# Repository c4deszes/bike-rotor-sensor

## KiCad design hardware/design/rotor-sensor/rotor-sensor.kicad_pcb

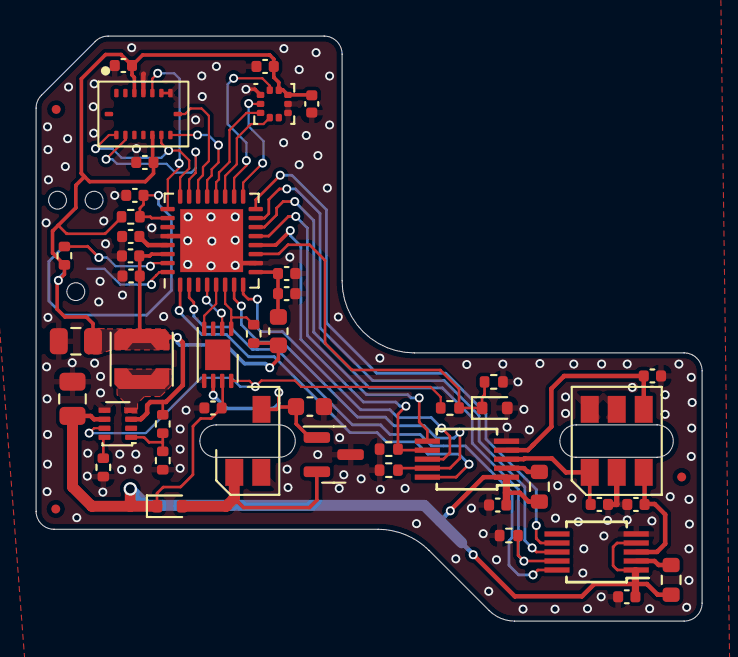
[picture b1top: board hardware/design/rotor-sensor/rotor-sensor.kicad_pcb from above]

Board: 2 copper layers, 37.0 x 32.5 mm, 50 parts (1 on the bottom side), 41 nets.

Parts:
C1, C2, C3, C6, C8, C9, C12, C15, C20, C23, C27, C600, C601: 100n; C_0402_1005Metric
C4, C5: 10u; C_0402_1005Metric
C7: 2.2u; C_0402_1005Metric
C10: 220p; C_0603_1608Metric
C11: 22u; C_0805_2012Metric
C16: 10u; C_0805_2012Metric
D1: BAS3005B02; D_SOD-523
D2: MM5Z3V6T1G; D_SOD-523
D4: SDT23C15L02; SOT-23
FID1, FID3, FID4: Fiducial; Fiducial_0.5mm_Mask1mm
J1: Conn_ARM_SWD_TagConnect_TC2030-NL; Tag-Connect_TC2030-IDC-NL_2x03_P1.27mm_Vertical
J2: Conn_01x06; SOIC-6
L1: 10uH; L_0603_1608Metric
L3: 2.2u; L_Coilcraft_LPS3010
R1, R3, R4, R6, R15, R17: 4.7k; R_0402_1005Metric
R2: 47k; R_0402_1005Metric
R5: 20k; R_0402_1005Metric
R7: 0; R_0402_1005Metric
R9, R18: 63.4k; R_0603_1608Metric
R12: 1k; R_0402_1005Metric
R13: 10k; R_0402_1005Metric
U1, U8: MAX9621AUB+T; MSOP-10_3x3mm_P0.5mm
U2: MCP2003BT-E/MC; DFN-8-1EP_3x2mm_P0.5mm_EP1.7x1.4mm
U3: BMI088; Bosch_LGA16
U6: TPS629210DRLR; SOT-583-8
U7: SOIC-4
U10: ATSAMD21E18A-MUT; VQFN-32-1EP_5x5mm_P0.5mm_EP3.5x3.5mm
U600: BMP581; Bosch_LGA10

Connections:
+3.3V: C4.2, C8.2, C9.1, C11.1, C12.2, C600.2, C601.2, J1.1 (VCC), L1.1, L3.2, R4.1, R5.1, R12.1, R13.1, U3.3 (VDD), U3.11 (VDDIO), U6.3 (VOS), U10.30 (VDDIN), U600.1 (VDDIO), U600.10 (VDD)
+BATT: C1.2, C2.2, C6.2, C16.2, D1.1 (K), R9.1, R18.1, U1.1 (BAT), U2.7 (V_{BB}), U6.6 (VIN), U8.1 (BAT), U8.4 (IN2)
/M03_EN: U2.2 (CS), U10.4 (PA03)
/M03_LINE: C10.1, D4.1 (K), U2.6 (L_{BUS}), U7.3
/M03_REGEN: R2.1, U2.8 (V_{REN}), U6.7 (EN)
/M03_RXD: R4.2, U2.1 (R_{XD}), U10.6 (PA05)
/M03_TXD: U2.4 (T_{XD}), U10.5 (PA04)
/M03_VMON: D2.1 (K), R2.2, R3.1, U10.11 (PA08)
/M04_IN1_IN: C3.2, J2.1, U1.3 (IN1)
/M04_IN2_IN: C27.2, J2.4, U1.4 (IN2)
/M04_IN3_IN: C23.2, J2.3, U8.3 (IN1)
/M04_INPUT1_DIAG/OE: R17.2, U1.9 (AOUT1), U10.7 (PA06)
/M04_INPUT1/~ERR: U1.8 (DOUT1), U10.8 (PA07)
/M04_INPUT2_DIAG/INPUT1: R15.2, U1.7 (AOUT2), U10.12 (PA09)
/M04_INPUT2/INPUT2: U1.6 (DOUT2), U10.13 (PA10)
/M04_INPUT3_DIAG/OE: R1.2, U8.9 (AOUT1), U10.14 (PA11)
/M04_INPUT3/~ERR: U8.8 (DOUT1), U10.15 (PA14)
/M04_NC/INPUT3: U8.7 (AOUT2), U10.16 (PA15)
/M04_~SLEEP1/DIAG1: U1.10 (~SLEEP), U10.1 (PA00)
/M04_~SLEEP2/DIAG2: U8.10 (~SLEEP), U10.2 (PA01)
/M05_BMI088_MOSI: U3.9 (SDI), U10.21 (PA22)
/M05_BMI088_SCK: U3.8 (SCK), U10.22 (PA23)
/M05_RESET: C20.2, J1.3 (~RESET), R13.2, U10.26 (~RESET)
/M05_SWCLK: J1.4 (SWCLK), R12.2, U10.31 (PA30)
/M05_SWDIO: J1.2 (SWDIO), U10.32 (PA31)
/M06_BMI088_CSA: U3.14 (CSB1), U10.23 (PA24)
/M06_BMI088_CSG: U3.5 (CSB2), U10.25 (PA27)
/M06_BMI088_MISO: U3.10 (SDO2), U3.15 (SDO1), U10.24 (PA25)
/M06_BMP581_CS: U10.19 (PA18), U600.6 (CSB)
/M06_BMP581_MISO: U10.20 (PA19), U600.5 (SDO)
/M06_BMP581_MOSI: U10.17 (PA16), U600.4 (SDI)
/M06_BMP581_SCK: U10.18 (PA17), U600.2 (SCK)
/TPS629210_FB: R5.2, R6.1, U6.1 (FB)
/TPS629210_MODE: R7.1, U6.8 (MODE)
/TPS629210_SW: L3.1, U6.4 (SW)
/VDDANA: C5.2, C15.2, L1.2, U10.9 (VDDANA)
/VDDCORE: C7.2, U10.29 (VDDCORE)
GND: C1.1, C2.1, C3.1, C4.1, C5.1, C6.1, C7.1, C8.1, C9.2, C10.2, C11.2, C12.1, C15.1, C16.1, C20.1, C23.1, C27.1, C600.1, C601.1, D2.2 (A), D4.3 (A), J1.5 (GND), J2.2, J2.5, J2.6, R1.1, R3.2, R6.2, R7.2, R15.1, R17.1, U1.5 (GND), U2.5 (V_{SS}), U3.4 (GND), U3.6 (GNDIO), U3.7 (PS), U6.5 (GND), U7.2, U8.5 (GND), U10.10 (GND), U10.28 (GND), U10.33 (GND), U600.3 (GND), U600.8 (GND), U600.9 (GND)
unnamed: R18.2, U1.2 (ISET)
unnamed: R9.2, U8.2 (ISET)
VS: D1.2 (A), D4.2 (K), U7.1

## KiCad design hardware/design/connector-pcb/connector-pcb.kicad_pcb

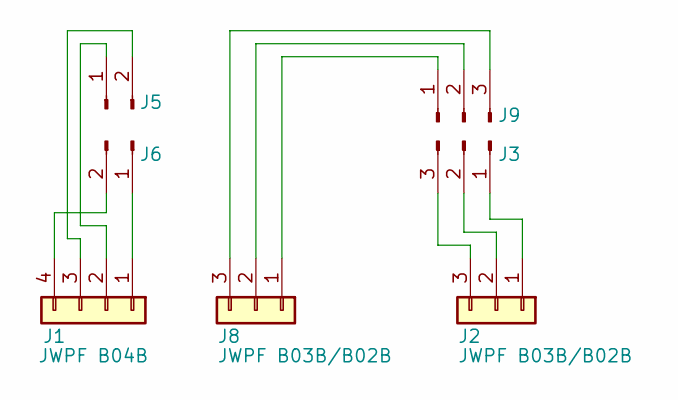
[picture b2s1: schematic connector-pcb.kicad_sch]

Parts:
J1: JWPF B04B; JST_JWPF_B04B-JWPF-SK-R_1x04_P2.00mm_Vertical
J2, J8: JWPF B03B/B02B; JST_JWPF_B03B-JWPF-SK-R_1x03_P2.00mm_Vertical
J3, J9: Conn_01x03_Pin; SMD_3PIN
J5, J6: Conn_01x02_Pin; SMD_2PIN

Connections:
unnamed: J1.1, J6.1
unnamed: J1.2, J5.1
unnamed: J1.3, J5.2
unnamed: J1.4, J6.2
unnamed: J2.1, J3.1
unnamed: J2.2, J3.2
unnamed: J2.3, J3.3
unnamed: J8.1, J9.1
unnamed: J8.2, J9.2
unnamed: J8.3, J9.3

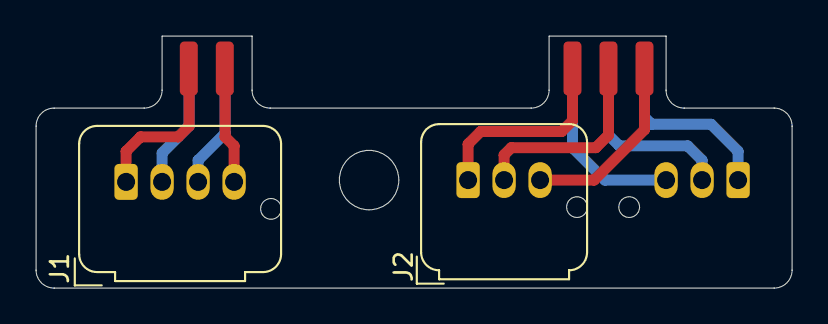
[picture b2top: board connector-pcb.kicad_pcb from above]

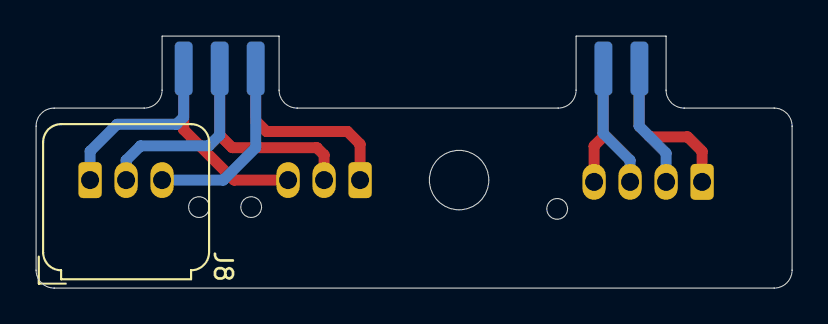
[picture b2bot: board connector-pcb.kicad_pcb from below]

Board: 2 copper layers, 42.0 x 14.0 mm, 7 parts (3 on the bottom side), 10 nets.

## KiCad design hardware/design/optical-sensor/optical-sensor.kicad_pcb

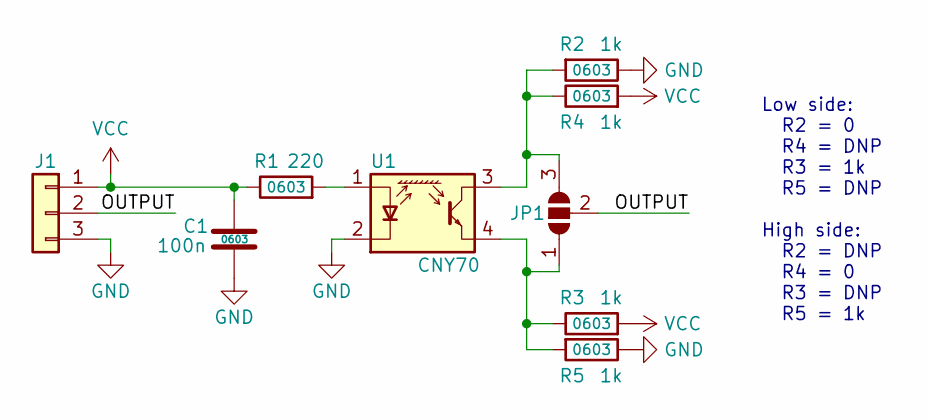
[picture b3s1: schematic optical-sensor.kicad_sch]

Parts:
C1: 100n; C_0603_1608Metric
J1: PinHeader_1x03_P2.54mm_Vertical
JP1: SolderJumper_3_Open; SolderJumper-3_P1.3mm_Open_RoundedPad1.0x1.5mm
R1: 220; R_0603_1608Metric
R2, R3, R4, R5: 1k; R_0603_1608Metric
U1: CNY70; Vishay_CNY70

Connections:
/OUTPUT: J1.2, JP1.2 (C)
/OUTPUT_H: JP1.3 (B), R2.2, R4.1, U1.3 (C); also elsewhere on the board
GND: C1.2, J1.3, R2.1, R5.1, U1.2 (K); also elsewhere on the board
unnamed: JP1.1 (A), R3.1, R5.2, U1.4 (E)
unnamed 4: R1.2, U1.1 (A); also elsewhere on the board
VCC: C1.1, J1.1, R1.1, R3.2, R4.2

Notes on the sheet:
Low side: R2 = 0 R4 = DNP R3 = 1k R5 = DNP High side: R2 = DNP R4 = 0 R3 = DNP R5 = 1k

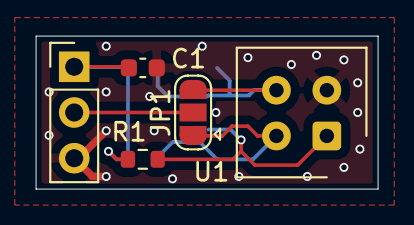
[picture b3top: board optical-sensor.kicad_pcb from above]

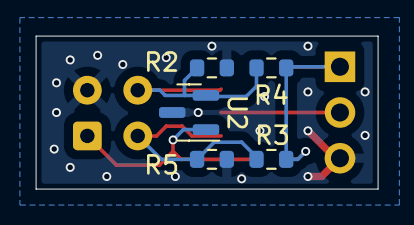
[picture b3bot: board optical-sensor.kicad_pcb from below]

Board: 2 copper layers, 19.0 x 8.5 mm, 10 parts (5 on the bottom side), 6 nets.

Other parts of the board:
U2: SM353LT; SOT-23

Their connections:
/OUTPUT_H: U2.2 (OUTPUT); also elsewhere on the board
GND: U2.3 (GND); also elsewhere on the board
unnamed 4: U2.1 (VCC); also elsewhere on the board

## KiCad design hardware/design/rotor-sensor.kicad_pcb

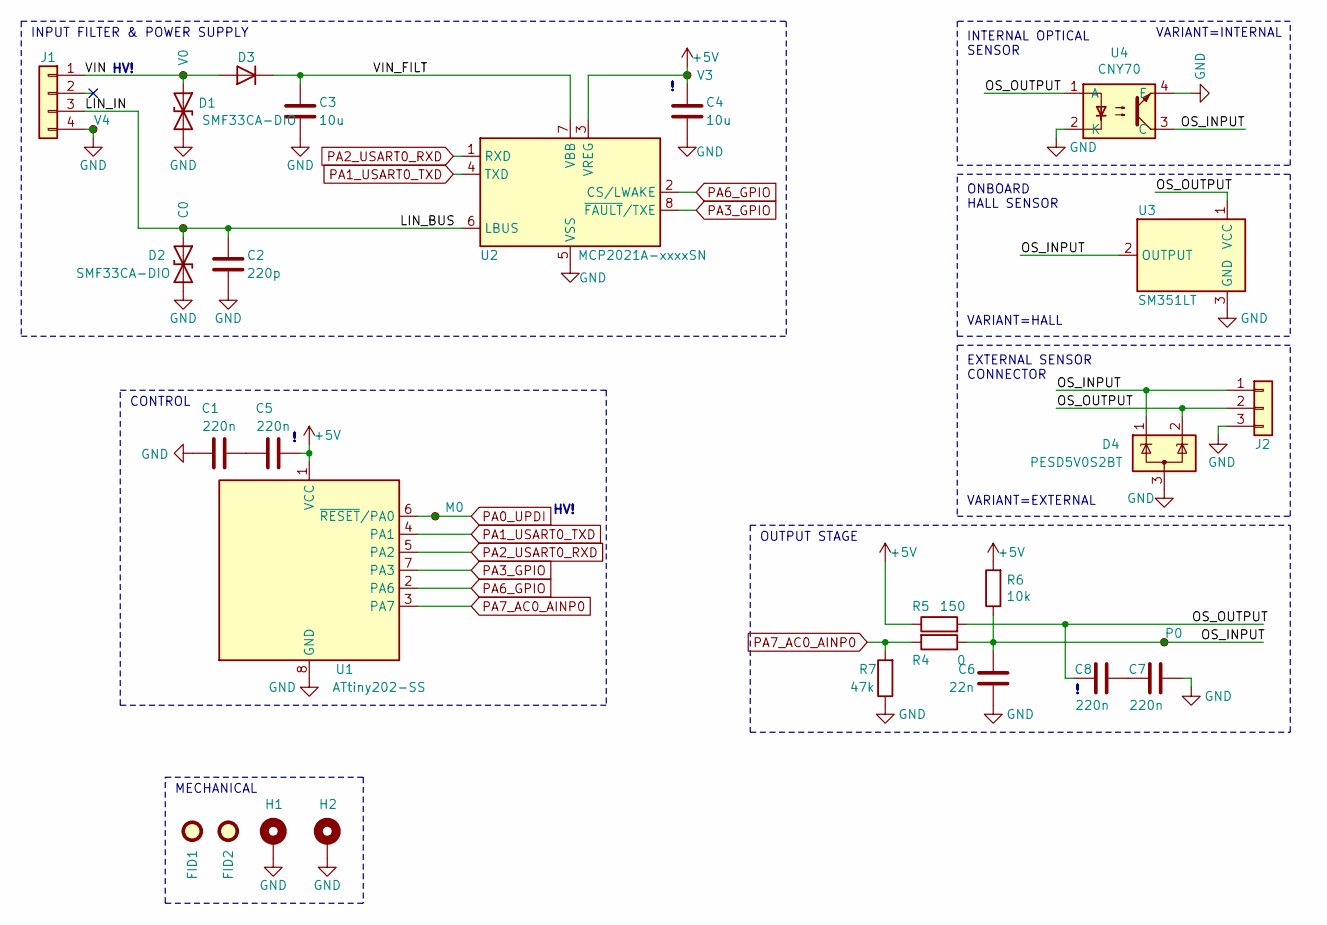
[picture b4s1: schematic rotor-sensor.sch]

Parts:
C1, C5, C7, C8: 220n; C_0402_1005Metric
C2: 220p; C_0603_1608Metric
C3, C4: 10u; C_0805_2012Metric; Voltage 25V; Part CL21A106KAYNNNG
C6: 22n; C_0603_1608Metric
D1, D2: SMF33CA-DIO; D_SMF
D3: BAS3005B02VH6327XT; D_SOD-523
D4: PESD5V0S2BT; SOT-23
FID1, FID2: Fiducial; Fiducial_0.5mm_Mask1.5mm
H1, H2: MountingHole_Pad; MountingHole_2.2mm_M2_DIN965_Pad_TopOnly
J1: Conn_01x04; JST_JWPF_B04B-JWPF-SK-R_1x04_P2.00mm_Vertical
J2: Conn_01x03; PinHeader_1x03_P2.54mm_Vertical
R4: 0; R_0402_1005Metric
R5: 150; R_0603_1608Metric
R6: 10k; R_0402_1005Metric
R7: 47k; R_0402_1005Metric
TP1: V4; TestPoint_Pad_D1.0mm
TP2: V0; TestPoint_Pad_D1.0mm
TP3: C0; TestPoint_Pad_D1.0mm
TP6: M0; TestPoint_Pad_D1.0mm
TP12: V3; TestPoint_Pad_D1.0mm
TP14: P0; TestPoint_Pad_D1.0mm
U1: ATtiny202-SS; SOIC-8_3.9x4.9mm_P1.27mm
U2: MCP2021A-xxxxSN; SOIC-8_3.9x4.9mm_P1.27mm
U3: SM351LT; SOT-23
U4: CNY70

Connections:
+5V: C4.1, C5.1, R5.1, R6.2, TP12.1, U1.1 (VCC), U2.3 (VREG)
/LIN_BUS: C2.1, D2.1 (A1), J1.3, TP3.1, U2.6 (LBUS)
/OS_INPUT: C6.1, D4.1 (K), J2.1, R4.1, R6.1, TP14.1, U3.2 (OUTPUT), U4.3 (C)
/OS_OUTPUT: C8.2, D4.2 (K), J2.2, R5.2, U3.1 (VCC), U4.1 (A)
/VIN: D1.1 (A1), D3.2 (A), J1.1, TP2.1
/VIN_FILT: C3.1, D3.1 (K), U2.7 (VBB)
GND: C1.2, C2.2, C3.2, C4.2, C6.2, C7.1, D1.2 (A2), D2.2 (A2), D4.3 (A), H1.1, H2.1, J1.4, J2.3, R7.1, TP1.1, U1.8 (GND), U2.5 (VSS), U3.3 (GND), U4.2 (K), U4.4 (E)
unnamed: C1.1, C5.2
unnamed: C7.2, C8.1
PA0_UPDI: TP6.1, U1.6 (~RESET~/PA0)
PA1_USART0_TXD: U1.4 (PA1), U2.4 (TXD)
PA2_USART0_RXD: U1.5 (PA2), U2.1 (RXD)
PA3_GPIO: U1.7 (PA3), U2.8 (~FAULT~/TXE)
PA6_GPIO: U1.2 (PA6), U2.2 (CS/LWAKE)
PA7_AC0_AINP0: R4.2, R7.2, U1.3 (PA7)

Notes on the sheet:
OUTPUT STAGE
ONBOARD HALL SENSOR
EXTERNAL SENSOR CONNECTOR
VARIANT=EXTERNAL
INTERNAL OPTICAL SENSOR
VARIANT=INTERNAL
VARIANT=HALL
MECHANICAL
HV!
CONTROL
INPUT FILTER & POWER SUPPLY

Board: 2 copper layers, 32 parts (7 on the bottom side), 15 nets, no tracks yet.

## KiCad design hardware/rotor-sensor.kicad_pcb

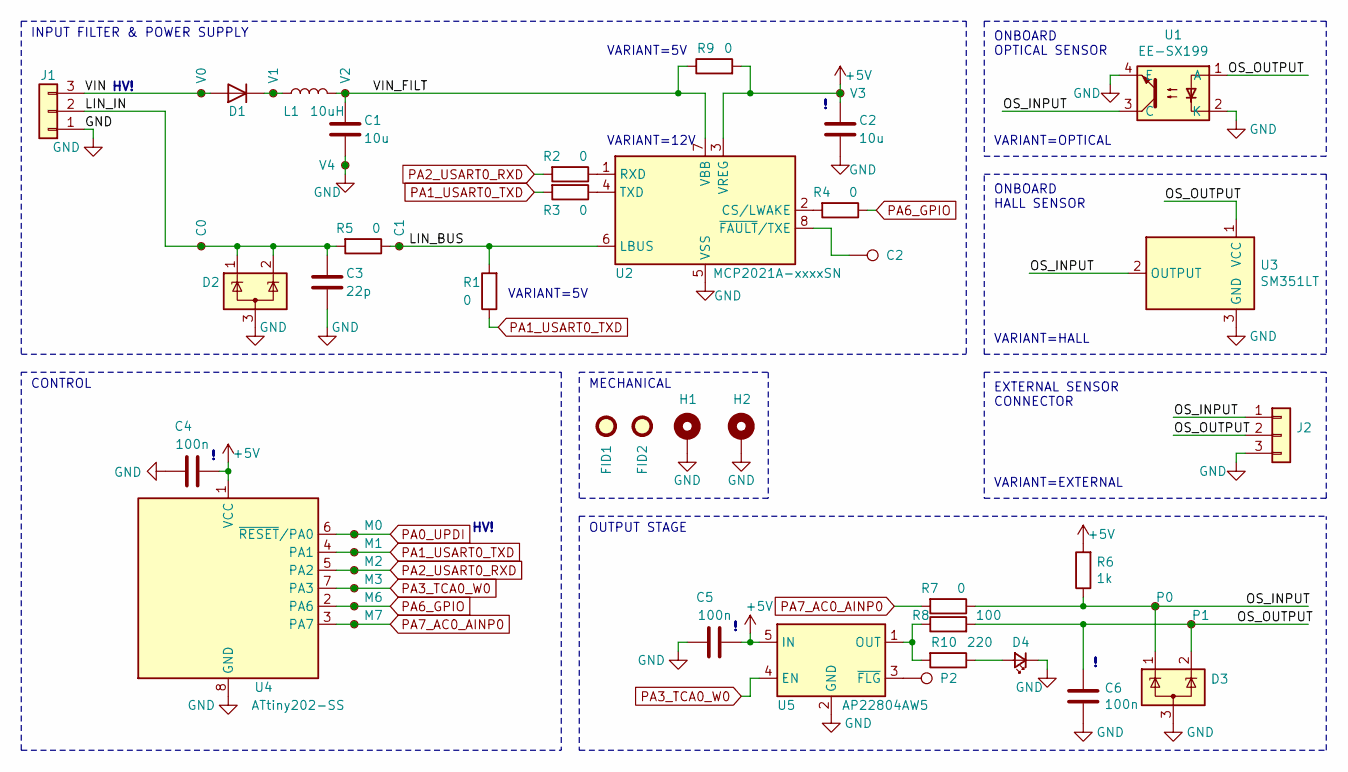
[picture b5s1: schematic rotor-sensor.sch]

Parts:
C1, C2: 10u; C_1206_3216Metric
C3: 22p; C_0603_1608Metric
C4, C5, C6: 100n; C_0603_1608Metric
D1: D; D_0805_2012Metric
D2, D3: SP0502BAHT; SOT-23
D4: LED_Small; LED_0603_1608Metric
FID1, FID2: Fiducial; Fiducial_0.5mm_Mask1.5mm
H1, H2: MountingHole_Pad; MountingHole_2.2mm_M2_DIN965_Pad_TopOnly
J1: Conn_01x03; JST_PH_B3B-PH-K_1x03_P2.00mm_Vertical
J2: Conn_01x03; PinHeader_1x03_P2.54mm_Vertical
L1: 10uH; L_0603_1608Metric
R1, R2, R3, R4, R5, R7: 0; R_0402_1005Metric
R6: 1k; R_0603_1608Metric
R8: 100; R_0603_1608Metric
R9: 0; R_0603_1608Metric
R10: 220; R_0603_1608Metric
TP1: V0; TestPoint_Pad_D1.0mm
TP2: V1; TestPoint_Pad_D1.0mm
TP3: V2; TestPoint_Pad_D1.0mm
TP4: V3; TestPoint_Pad_D1.0mm
TP5: V4; TestPoint_Pad_D1.0mm
TP6: C0; TestPoint_Pad_D1.0mm
TP7: C1; TestPoint_Pad_D1.0mm
TP8: C2; TestPoint_Pad_D1.0mm
TP9: M0; TestPoint_Pad_D1.0mm
TP10: M1; TestPoint_Pad_D1.0mm
TP11: M2; TestPoint_Pad_D1.0mm
TP12: M3; TestPoint_Pad_D1.0mm
TP13: M6; TestPoint_Pad_D1.0mm
TP14: P0; TestPoint_Pad_D1.0mm
TP15: M7; TestPoint_Pad_D1.0mm
TP16: P1; TestPoint_Pad_D1.0mm
TP17: P2; TestPoint_Pad_D1.0mm
U1: EE-SX199
U2: MCP2021A-xxxxSN; SOIC-8_3.9x4.9mm_P1.27mm
U3: SM351LT; SOT-23
U4: ATtiny202-SS; SOIC-8_3.9x4.9mm_P1.27mm
U5: AP22804AW5; SOT-23-5

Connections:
+5V: C2.1, C4.1, C5.2, R6.2, R9.2, TP4.1, U2.3 (VREG), U4.1 (VCC), U5.5 (IN)
/LIN_BUS: R1.2, R5.1, TP7.1, U2.6 (LBUS)
/LIN_IN: C3.1, D2.1 (K), D2.2 (K), J1.2, R5.2, TP6.1
/OS_INPUT: D3.1 (K), J2.1, R6.1, R7.1, TP14.1, U1.3 (C), U3.2 (OUTPUT)
/OS_OUTPUT: C6.1, D3.2 (K), J2.2, R8.2, TP16.1, U1.1 (A), U3.1 (VCC)
/VIN: D1.2 (A), J1.3, TP1.1
/VIN_FILT: C1.1, L1.2, R9.1, TP3.1, U2.7 (VBB)
GND: C1.2, C2.2, C3.2, C4.2, C5.1, C6.2, D2.3 (A), D3.3 (A), D4.1 (K), H1.1, H2.1, J1.1, J2.3, TP5.1, U1.2 (K), U1.4 (E), U2.5 (VSS), U3.3 (GND), U4.8 (GND), U5.2 (GND)
unnamed: D1.1 (K), L1.1, TP2.1
unnamed: D4.2 (A), R10.1
unnamed: R2.1, U2.1 (RXD)
unnamed: R3.1, U2.4 (TXD)
unnamed: R4.2, U2.2 (CS/LWAKE)
unnamed: R8.1, R10.2, U5.1 (OUT)
unnamed: TP8.1, U2.8 (~FAULT~/TXE)
unnamed: TP17.1, U5.3 (~FLG)
PA0_UPDI: TP9.1, U4.6 (~RESET~/PA0)
PA1_USART0_TXD: R1.1, R3.2, TP10.1, U4.4 (PA1)
PA2_USART0_RXD: R2.2, TP11.1, U4.5 (PA2)
PA3_TCA0_W0: TP12.1, U4.7 (PA3), U5.4 (EN)
PA6_GPIO: R4.1, TP13.1, U4.2 (PA6)
PA7_AC0_AINP0: R7.2, TP15.1, U4.3 (PA7)

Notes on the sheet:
INPUT FILTER & POWER SUPPLY
OUTPUT STAGE
ONBOARD HALL SENSOR
EXTERNAL SENSOR CONNECTOR
ONBOARD OPTICAL SENSOR
VARIANT=HALL
VARIANT=EXTERNAL
VARIANT=OPTICAL
MECHANICAL
CONTROL
HV!
VARIANT=5V
VARIANT=12V

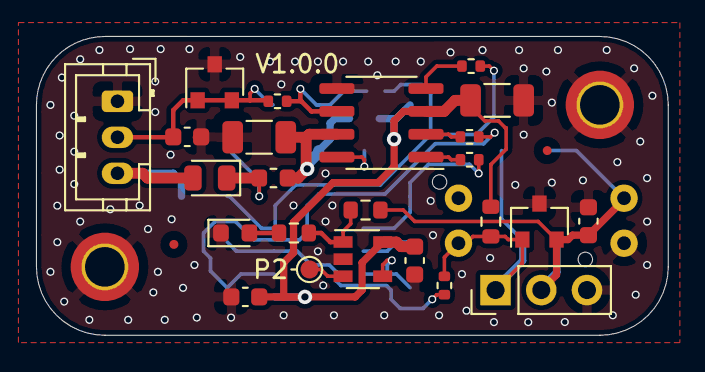
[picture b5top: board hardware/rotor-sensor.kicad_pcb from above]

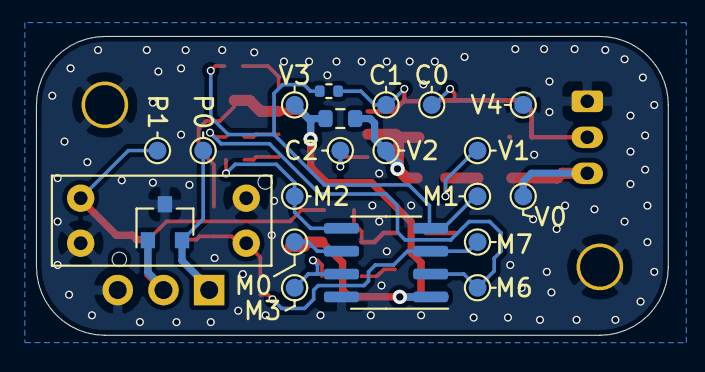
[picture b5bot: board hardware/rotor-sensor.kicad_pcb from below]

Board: 2 copper layers, 35.1 x 16.6 mm, 49 parts (21 on the bottom side), 22 nets.

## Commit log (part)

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2021-09-25 Initial commit
    Adds software components and workflow
2021-09-25 Some stuff
2021-09-25 Moves software workflow to the correct folder
2021-09-25 Fixes CMake presets
2021-10-10 Software update
    Updates application profiles
    Adds signals and rpc code generator tool
    Scheduler changed to only have 1ms and 10ms tasks
    Documents a bunch of low level components
2021-10-19 Merges sensor library into application
    Adds RTC component
2021-10-20 Initial hardware commit
2021-10-20 Fixes DRC errors
2021-10-26 Usart configuration
    Baudrate is now calculated
2021-10-27 Updates docker image version
2021-10-27 Debugging workflow
2021-10-28 Bumps docker image version used in software build workflow
2021-10-28 Bumps image version in devcontainer config
2021-10-30 Initial hardware commit (#2)
2021-10-30 Software refactoring and documentation (#1)
    * Moves software workflow to the correct folder
    * Adds signals and rpc code generator tool
    * Scheduler changed to only have 1ms and 10ms tasks
    * Documents a bunch of low level components
    * Merges sensor library into application
    * Adds RTC component
2021-10-31 Execution rights of hardware scripts
2021-11-01 Consolidates workflow execution
    Workflow now runs for the different variants.
    The KiBot configuration has been merged into a single file.
2021-11-01 Updates hardware scripts
2021-11-01 Archival of all variant outputs
2021-11-01 Rotated input filter capacitor for better ground connection
2021-11-03 Adds panelization job
    Renamed the existing workflows
2021-11-03 Replaces docker image in panelization step
2021-11-05 Panelization workflow updates
    Adds fiducials to board and added tab annotation as a footprint.
    Panel configuration has been updated.
2021-11-05 Fixes manufacturing panelized job
2021-11-05 Second hardware iteration (#3)
    Cleaned up the schematic and reworked the entire PCB.
    Replaced EE-SX1083 with EE-SX199, added 3D model and new component.
    Added modified worksheet so that the PCB origin can be 0, 0.
    Added scripts to execute certain tasks locally and updated the workflow accordingly.
    Workflow now runs for the different variants.
    The KiBot configuration has been merged into a single file.
2021-11-05 Documentation changes
    CMakePresets have been updated
2021-11-06 CMake preset rework
    BSP uart config now depends on the board variant
    Minor documentation changes
2021-11-06 Fixes workflow
2021-11-06 BSP correctly selects the MCU type based on board type
    Prints out configuration
2021-11-06 Documentation changes (#4)
    CMakePresets and configuration mechanism have been updated
    BSP UART config now depends on the board variant
    BSP correctly selects the MCU type based on board type
2021-11-11 Working bootloader with jump functionality
2021-11-11 Parallel application and standalone application linking
    Removes option to enable the bootloader in the application code.
    Adds application helper cmake file that can generate hex, bin, etc.
    Renamed bootloader target to isolate it from the application.
    LTO is now enabled for all non debug variants.
2021-11-12 Updates CI image
2021-11-13 Adds CRC scan peripheral to HAL
2021-11-14 Adds unit and SIL tests
    All packages have been updated to allow testing on PC
2021-11-14 Bootloader development (#5)
    Updated existing profiles and added build presets for bootloader development.
    Application can be merged with the bootloader hex file.
    Scheduler now has default task, so 1ms and 10ms don't have to be defined.
    Added CPUINT component to HAL that allows Interrupt vector table selection.
    Software reset uses CCP to access the SWRR register.
    Working bootloader with jump functionality
2021-11-15 Fake HAL initial implementation
2021-11-22 Software Testing (#6)
    * Adds unit and SIL tests
    * All packages have been updated to allow testing on PC
    * Fake HAL initial implementation
2021-11-27 Bootloader flashing functionality
    Fixes application region length
    Bootloader responsibilities has been separated into multiple files.
    Added CCP SPM unlocking function
2021-12-12 Making the software work again
    Fixes application region size in the Bootloader
    Implements User LED functions
    Fixes typo in Input stage handler analog variant
    TCB now uses the syncup feature and ISH will also initialize TCA
    Fixes Usart byte size in full duplex mode
2022-03-20 Sensors working, added temp. sensing
2022-04-09 Hardware container version downgrade
2022-04-09 Downgrade to KiCad 5.1.6
2022-04-09 Debian?
2022-04-10 Download?
2022-04-10 Updated Kibot installation
2022-04-10 Fix install command
2022-04-10 Removes 3D gen. step
2022-04-10 Disable panelization
2022-04-10 Kikit downgrade
2022-04-10 KiKit docker image downgrade
2022-04-13 Panelize?
2022-04-15 Retention day set to 5 days
    Hidden LED type on Fab layer
2022-04-17 Tight frame and 1x4 panel layout
2022-04-17 Panelized drill
2022-05-01 Adds LIN Transceiver to the design (#7)
    Updates layout and schematic, replaced test point labels on schematic
    Adds overcurrent protection IC and removes sense line
    Hardware container version downgrade, KiKit downgrade
    Hardware workflow retention day set to 5 days and
    STEP generation step is skipped due to errors
    Fixes track clearance issue on panelized layout
2022-05-22 LIN Trans. power down mode
    Consolidates VCOM pins, added CS pin
    Disables temperature measurement
    Removes OSH current measurement
2022-11-27 Sensor calculation
    Changed sensor parameter flow
    Disabled position estimator
    Disabled TCB TCA syncup
2022-11-27 Fix osccfg checking
2022-11-30 Removes bootloader target from presets
2022-11-30 New sensor settings (#8)
    * Making the software work again
    Fixes application region size in the Bootloader
    Implements User LED functions
    Fixes typo in Input stage handler analog variant
    TCB now uses the syncup feature and ISH will also initialize TCA
    Fixes Usart byte size in full duplex mode
2022-11-30 Initial system documents
2022-11-30 Initial system documents (#9)
2022-11-30 PCB test probe schematic (#10)
2022-12-29 Communication format changes
2023-01-01 Mechanical parts and tools
2023-05-24 New hardware design
    - Dual PCB construction
    - 2 Channel speed sensing using 2 or 3 wire hall/optical sensors
    - Included IMU
    - More powerful processor
2023-05-24 Kicad7 sch file extension update
2023-05-24 Workflow container update
2023-05-24 Disabling ERC
2023-05-24 Disable DRC
2023-05-24 Disabling variants
2023-05-24 New docker images
2023-05-29 Finalizing hardware design
2023-05-29 Missing drill file
2023-05-29 Fab. layer cleanup
2023-05-31 Initial documentation
2023-06-01 Sphinx needs extension
2023-06-01 Removing Kroki diagram
2023-06-01 schemdraw dependency
2023-06-01 MIssing dependency
2023-06-07 FInalization
    RPP Diode doc update and calculation
    Sensor description
    Fixes missing sphinx plugin
2023-06-08 Gen2 Hardware design (#11)
    - Dual PCB construction
    - 2 Channel speed sensing using 2 or 3 wire hall/optical sensors
    - Included IMU
    - More powerful processor
2023-06-14 First software for Gen2 hardware
    TC4 captures period and width in us resolution
2023-09-11 Backup
2023-12-10 Working output stage control
    SEC - sensor initialization startup and state readback
    DFLL - Initialization moved to SYSCTRL
    PM - CPU and Bus clock division function
    BSP - Moved clock settings out of Init
    BSP - Moved pin settings to pinout.h
    EVSYS - Acquire channel function
2023-12-12 Working UART transmission
2023-12-12 Cleanup of USART TX
2023-12-14 Temporary fix for UART issue
2023-12-18 Speed measurement and signals
2023-12-18 Remapping timers
    Communication updates
2023-12-26 CS pin support, increasing pulse timeout to 10s
2024-01-01 Externalized network spec.
2024-01-01 Update submodule version
2024-02-17 CI workflow
2024-02-17 line-protocol version
2024-02-17 Submodules
2024-02-17 Setup line_protocol codegen
2024-02-17 New docker image
2024-02-18 Documentation
2024-02-18 Prototype software (#12)
    * TC3-4 captures period and width in us resolution
    * Working scheduler
    * Working output stage control
    * SEC - sensor initialization startup and state readback
    * DFLL - Initialization moved to SYSCTRL
    * PM - CPU and Bus clock division function
2024-02-18 Initial system requirements
2024-02-18 Initial system requirements (#13)
2024-02-24 Optical sensor adapter & CI workflow changes
2024-03-02 Fixes
2024-03-02 5V rail renamed to VCC Fixed size information on some resistors
2024-03-02 Fix silkscreen and increase millradius
2024-03-02 Hardware Gen2 design freeze (#14)
    * Fix label in connector schematic and added JWPF 3 pin connector
    * Optical sensor adapter & CI workflow changes
    * 5V rail renamed to VCC
    * Fixed size information on some resistors
    * Added Hall sensor position on PCB
2024-03-15 samd21-hal integration
2024-03-16 Bootloader integration
2024-04-24 Fix missing Python deps.
2024-04-24 Maybe?
2024-04-24 New bootloader, new HAL
2024-08-28 Speed calculation
2024-10-27 FInal ordered hardware
    New 3pin connector
    Extra 2pin connector for cadence measurement
    No 3pin sensor variant
    DC/DC converter for MCU
    Pressure sensor
2024-10-27 HAL and Bootloader integration (#15)
    * samd21-hal integration
    * Bootloader integration
    * System state machine, supports boot entry
    Fixed speed calculation?
    AP22802 support (untested)
    * Fix missing Python deps.
2024-10-27 Gen2 development halt (#17)
    * Gen2 Hardware design (#11)
    - Dual PCB construction
    - 2 Channel speed sensing using 2 or 3 wire hall/optical sensors
    - Included IMU
    - More powerful processor
    * Prototype software (#12)
2024-10-29 Pressure sensor and IMU
    Integrated both Bosch drivers
    Bootloader is disabled for now as it doesn't support
    the pins used in this project
2024-12-01 Working pressure sensor and IMU
    Integrated new bootloader
2024-12-04 Mostly working altitude measurement
2024-12-04 New signals
2024-12-14 Mostly working software
    Still has issues with speed measurement, works okayish above 15km/h
    Altitude measurement is not very accurate and the increments in large jumps
    Distance/Gear/Cadence not yet tested
    IMU does read the data but it's not used yet
2024-12-14 Better speed measurement
    Dropped resolution down to 100us as that still fits the spec.
    for 0.1km/h resolution in a single pole configuration.
    The 6.5sec maximum period is enough down to 1.2km/h
2024-12-22 Working speed, cadence and distance
2024-12-24 Cadence sensor diagnostics (preliminary)
2024-12-26 Working Ride state management TopSpeed and AvgSpeed calculations Initial speed is now correct
2024-12-28 Altitude lookup table
2025-01-25 Docs
2025-03-22 Software overhaul
    Separate configuration manager
    Software version updated from CMake
    Separate component for handling diagnostic callouts
    Gear estimation
2025-05-01 Fix missing metadata file
2025-05-01 Functional tests
2025-05-01 Help files
2025-05-11 System documentation rework for Gen2.1
2025-05-11 Software docs
2025-05-11 Mechanical design Uploading Gen1.0, Gen2.0, Gen2.1 files, including sensor holders
2025-06-09 Working supply voltage monitoring
2025-10-19 Disable ride log saving before sleep
2025-10-19 Pressure to altitude conversion script
2025-10-19 Latest electronics spec.
2025-10-19 Updating to latest library versions
2025-10-19 Fixing merge issues
2025-10-19 Setup UDS tool
2025-10-19 Sw/gen2.1 (#20)
    * Pressure sensor and IMU
    Integrated both Bosch drivers
    Bootloader is disabled for now as it doesn't support
    the pins used in this project
    * Working pressure sensor and IMU
    Integrated new bootloader
2025-10-19 Adds datasheets for Gen2.1 hardware components (#21)
2025-10-19 Fixes BMI088 and BMP581 3d models using absolute paths
